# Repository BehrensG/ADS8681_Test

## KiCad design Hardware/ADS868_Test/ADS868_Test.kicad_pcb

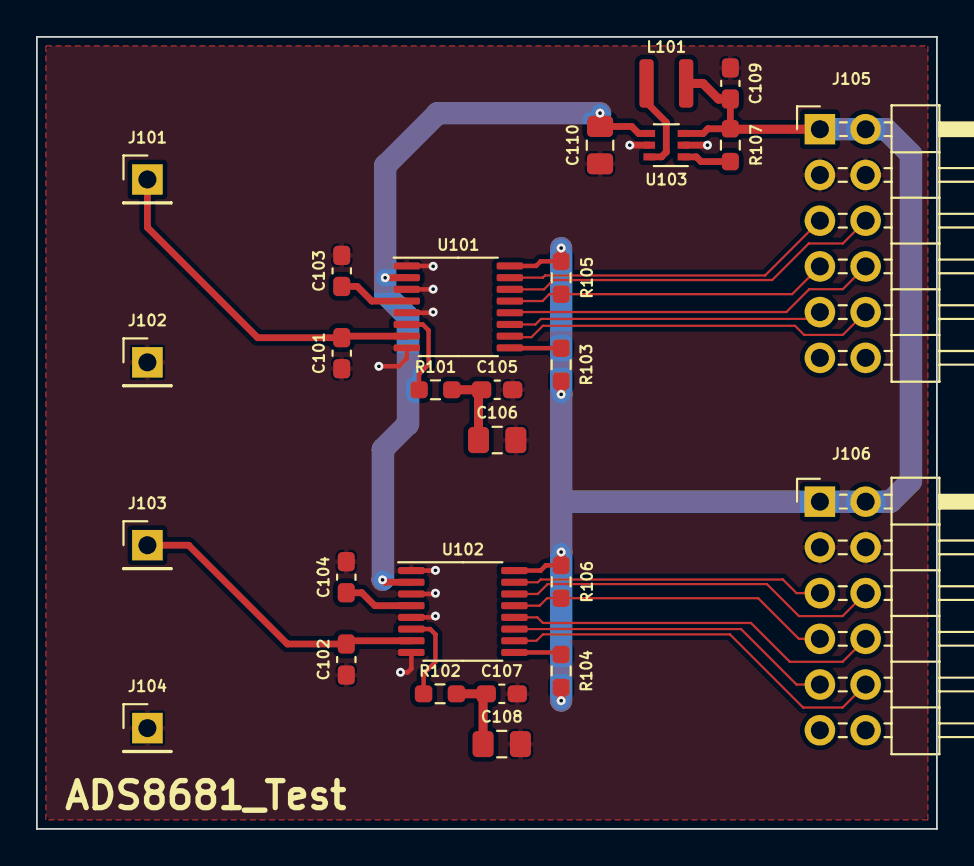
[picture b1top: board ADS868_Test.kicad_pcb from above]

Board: 2 copper layers, 50.0 x 44.0 mm, 27 parts (0 on the bottom side), 27 nets.

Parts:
C101, C102: 330p; C_0603_1608Metric_Pad1.08x0.95mm_HandSolder
C103, C104: 4u7; C_0603_1608Metric_Pad1.08x0.95mm_HandSolder
C105, C107, C109: 1u; C_0603_1608Metric_Pad1.08x0.95mm_HandSolder
C106, C108: 22u; C_0805_2012Metric_Pad1.18x1.45mm_HandSolder
C110: GRM21BR60J226ME39L; C_0805_2012Metric_Pad1.18x1.45mm_HandSolder
J101, J102, J103, J104: Conn_01x01; PinHeader_1x01_P2.54mm_Vertical
J105, J106: 71764-0012; PinHeader_2x06_P2.54mm_Horizontal
L101: locked; NRH3012
R101, R102: 0R22; R_0603_1608Metric_Pad0.98x0.95mm_HandSolder
R103, R104, R105, R106: 10k; R_0603_1608Metric_Pad0.98x0.95mm_HandSolder
R107: 0; R_0603_1608Metric_Pad0.98x0.95mm_HandSolder
U101, U102: ADS8681IPWR; TSSOP-16_4.4x5mm_P0.65mm
U103: LTC3525-5; SOT-363_SC-70-6

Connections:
+3V3: C109.1, J105.1, J105.2, J106.1, J106.2, L101.1, R103.1, R104.1, R105.1, R106.1, R107.1, U101.16 (DVDD), U102.16 (DVDD), U103.3 (VIN)
+5V: C110.1, U101.2 (AVDD), U102.2 (AVDD), U103.4 (VOUT)
/ADC1_RVS: J105.5, U101.15 (RVS)
/ADC1_SCLK: J105.8, U101.12 (SCLK)
/ADC1_SDI: J105.10, U101.10 (SDI)
/ADC1_SDO-0: J105.7, R105.2, U101.13 (SDO-0)
/ADC1_SDO-1: J105.6, U101.14 (SDO-1)
/ADC1_~CS: J105.9, U101.11 (CONVST/~CS)
/ADC2_RVS: J106.5, U102.15 (RVS)
/ADC2_SCLK: J106.8, U102.12 (SCLK)
/ADC2_SDI: J106.10, U102.10 (SDI)
/ADC2_SDO-0: J106.7, R106.2, U102.13 (SDO-0)
/ADC2_SDO-1: J106.6, U102.14 (SDO-1)
/ADC2_~CS: J106.9, U102.11 (CONVST/~CS)
GND: C101.2, C102.2, C103.1, C104.1, C105.2, C106.2, C107.2, C108.2, C109.2, C110.2, J102.1, J104.1, J105.3, J105.4, J106.3, J106.4, U101.1 (DGND), U101.3 (AGND), U101.5 (REFGND), U101.8 (AIN_GND), U102.1 (DGND), U102.3 (AGND), U102.5 (REFGND), U102.8 (AIN_GND), U103.2 (GND), U103.5 (GND)
unnamed: C105.1, C106.1, R101.2
unnamed: C107.1, C108.1, R102.2
unnamed: C101.1, J101.1, U101.7 (AIN_P)
unnamed: C102.1, J103.1, U102.7 (AIN_P)
unnamed: R101.1, U101.6 (REFCAP)
unnamed: C103.2, U101.4 (REFIO)
unnamed: R103.2, U101.9 (~RST)
unnamed: R102.1, U102.6 (REFCAP)
unnamed: C104.2, U102.4 (REFIO)
unnamed: R104.2, U102.9 (~RST)
unnamed: L101.2, U103.6 (SW)
unnamed: R107.2, U103.1 (~SHDN)

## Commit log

2023-08-09 Design
2023-08-26 Test
2023-08-28 Develop
2023-08-29 FPGA
2023-09-05 FPGA PSSI works
2025-01-19 Software
2025-01-27 Fixed AXI-SPI MISO data readout problem. Wrong io was used in Vivado, was io0_i should be io1_i.
2025-01-29 Replaced the snprintf with min_snprintf in SCPI parser library.
2025-05-03 New SCPI functions
2025-05-04 Bug fixes
